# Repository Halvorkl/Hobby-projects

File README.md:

# Hobby-projects

This repository contains smaller hobby projects I've worked on, mainly within electronics and hardware design.

I mostly focus on:

- PCB design
- IC design
- General system design (electronics and embedded-related)

The projects here are experiments, prototypes, and explorations of different ideas and design techniques.

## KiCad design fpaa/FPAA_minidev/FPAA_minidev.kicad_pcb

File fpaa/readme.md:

## FPAA dev board

In this project, I have designed a compact development board for the AN231.

The AN231 is a Field Programmable Analog Array (FPAA) based on a switched-capacitor architecture. It enables a programmable analog front-end in your design, allowing the same hardware to be repurposed for different analog signal processing tasks.

This project provides a simple, compact PCB that can be easily integrated into other designs. The board has a form factor of ~47x21.2mm, and the I/O connections are kept as straightforward as possible to simplify prototyping and implementation.

<p float="left">
  
  &nbsp;&nbsp;
  
</p>

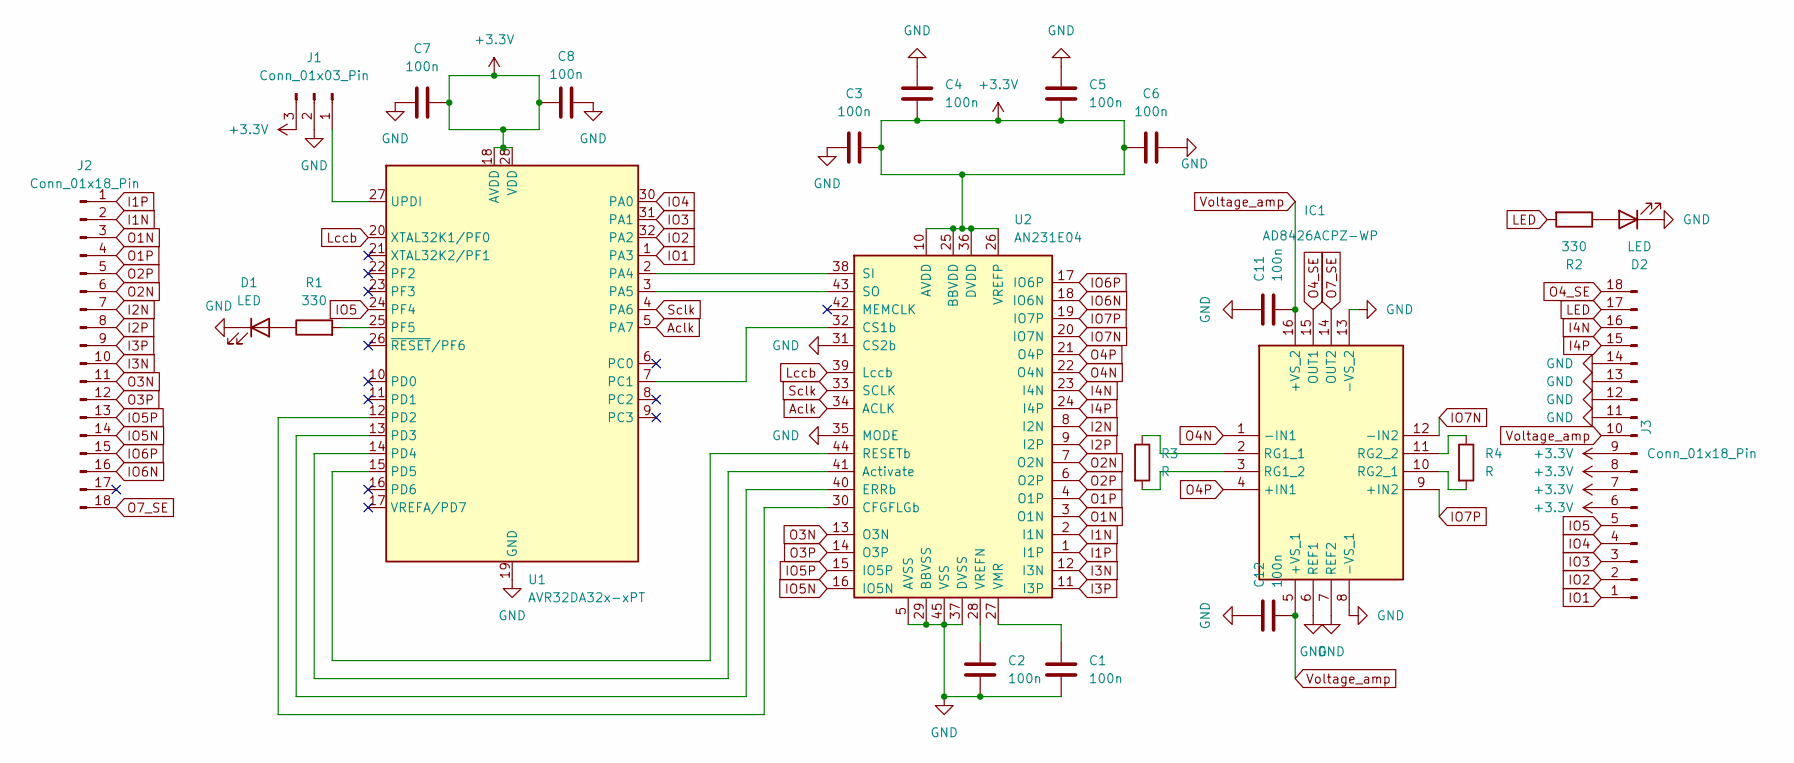
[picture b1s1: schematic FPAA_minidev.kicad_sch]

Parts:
C1, C2, C3, C4, C5, C6, C7, C8, C11, C12: 100n; C_0603_1608Metric
D1, D2: LED; LED_0603_1608Metric
IC1: AD8426ACPZ-WP; QFN65P400X400X100-16N-D; Mouser Part Number 584-AD8426ACPZ-WP
J1: Conn_01x03_Pin; PinHeader_1x03_P2.54mm_Vertical
J2, J3: Conn_01x18_Pin; PinHeader_1x18_P2.54mm_Vertical
R1, R2: 330; C_0603_1608Metric
R3, R4: R; C_0603_1608Metric
U1: AVR32DA32x-xPT; TQFP-32_7x7mm_P0.8mm
U2: AN231E04; QFN-44-1EP_9x9mm_P0.65mm_EP7.5x7.5mm

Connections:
+3.3V: C3.1, C4.2, C5.2, C6.1, C7.2, C8.1, J1.3, J3.6, J3.7, J3.8, J3.9, U1.18 (AVDD), U1.28 (VDD), U2.10 (AVDD), U2.25 (BBVDD), U2.26 (VREFP), U2.36 (DVDD)
Aclk: U1.5 (PA7), U2.34 (ACLK)
GND: C1.2, C2.2, C3.2, C4.1, C5.1, C6.2, C7.1, C8.2, C11.1, C12.1, D1.1 (K), D2.1 (K), IC1.6 (REF1), IC1.7 (REF2), IC1.8 (-VS_1), IC1.13 (-VS_2), J1.2, J3.11, J3.12, J3.13, J3.14, U1.19 (GND), U1.29 (GND), U2.5 (AVSS), U2.29 (BBVSS), U2.31 (CS2b), U2.35 (MODE), U2.37 (DVSS), U2.45 (VSS)
I1N: J2.2, U2.2 (I1N)
I1P: J2.1, U2.1 (I1P)
I2N: J2.7, U2.8 (I2N)
I2P: J2.8, U2.9 (I2P)
I3N: J2.10, U2.12 (I3N)
I3P: J2.9, U2.11 (I3P)
I4N: J3.16, U2.23 (I4N)
I4P: J3.15, U2.24 (I4P)
IO1: J3.1, U1.1 (PA3)
IO2: J3.2, U1.32 (PA2)
IO3: J3.3, U1.31 (PA1)
IO4: J3.4, U1.30 (PA0)
IO5: J3.5, U1.24 (PF4)
IO5N: J2.14, U2.16 (IO5N)
IO5P: J2.13, U2.15 (IO5P)
IO6N: J2.16, U2.18 (IO6N)
IO6P: J2.15, U2.17 (IO6P)
IO7N: IC1.12 (-IN2), U2.20 (IO7N)
IO7P: IC1.9 (+IN2), U2.19 (IO7P)
LED: J3.17, R2.2
Lccb: U1.20 (XTAL32K1/PF0), U2.39 (Lccb)
unnamed: D1.2 (A), R1.1
unnamed: D2.2 (A), R2.1
unnamed: IC1.2 (RG1_1), R3.1
unnamed: IC1.3 (RG1_2), R3.2
unnamed: IC1.10 (RG2_1), R4.2
unnamed: IC1.11 (RG2_2), R4.1
unnamed: J1.1, U1.27 (UPDI)
unnamed: U1.2 (PA4), U2.38 (SI)
unnamed: U1.3 (PA5), U2.43 (SO)
unnamed: U1.7 (PC1), U2.32 (CS1b)
unnamed: U1.12 (PD2), U2.30 (CFGFLGb)
unnamed: U1.13 (PD3), U2.40 (ERRb)
unnamed: U1.14 (PD4), U2.41 (Activate)
unnamed: U1.15 (PD5), U2.44 (RESETb)
unnamed: R1.2, U1.25 (PF5)
unnamed: C1.1, U2.27 (VMR)
unnamed: C2.1, U2.28 (VREFN)
O1N: J2.3, U2.3 (O1N)
O1P: J2.4, U2.4 (O1P)
O2N: J2.6, U2.7 (O2N)
O2P: J2.5, U2.6 (O2P)
O3N: J2.11, U2.13 (O3N)
O3P: J2.12, U2.14 (O3P)
O4N: IC1.1 (-IN1), U2.22 (O4N)
O4P: IC1.4 (+IN1), U2.21 (O4P)
O4_SE: IC1.15 (OUT1), J3.18
O7_SE: IC1.14 (OUT2), J2.18
Sclk: U1.4 (PA6), U2.33 (SCLK)
Voltage_amp: C11.2, C12.2, IC1.5 (+VS_1), IC1.16 (+VS_2), J3.10

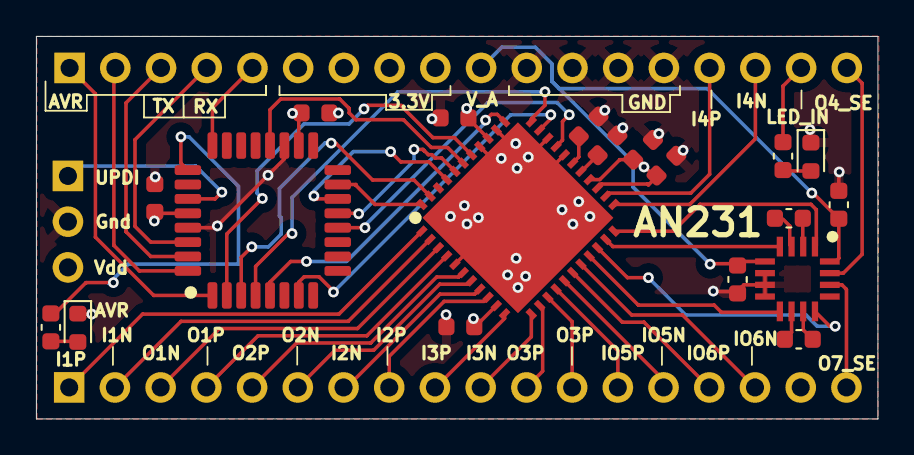
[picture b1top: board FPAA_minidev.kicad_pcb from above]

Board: 4 copper layers, 46.8 x 21.2 mm, 22 parts (0 on the bottom side), 53 nets.

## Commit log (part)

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2026-06-21 Enhance README with project descriptions and focus areas
    Expanded the README to provide more details about the projects.
2026-06-21 Add initial README for Radar project
2026-06-21 Add description to radar project README
2026-06-21 Update readme for clarity and formatting
2026-06-21 Add readme for 5 GHz CW radar project
    This document outlines the objectives and focus areas of the 5 GHz CW radar project, emphasizing the analog front-end design.
2026-06-21 Create README for Wi-Fi radar project
    Added project overview and goals for Wi-Fi radar.
2026-06-21 Update readme to clarify signal source description
2026-06-21 Create README for FPAA development board
    Added a README file for the FPAA development board, detailing its design and functionality.
2026-06-21 Add readme for Lyra – GHOST mission communications system
    Added project overview and details about the CubeSat communications system.
2026-06-21 Added pcb and belonging files
2026-06-21 zipped pcb files
2026-06-21 Include front view image in readme
    Add image reference for PCB front view in readme.
2026-06-21 Fix image filename case in readme.md
2026-06-21 Improve layout of PCB images in readme
    Added margin to the front PCB image for better layout.
2026-06-21 Adjust image margin in readme
    Updated the margin of the front PCB image for better layout.
2026-06-21 Adjust PCB image layout in readme
    Removed excessive margin from front PCB image.
2026-06-21 Enhance readme with image descriptions
    Added descriptions for front and back images of PCB.
2026-06-21 Update readme.md to improve PCB image display
    Replaced old image formatting with a table layout for better presentation.
2026-06-21 Fix image source case in readme.md
2026-06-21 Revise PCB images in readme for better layout
    Updated the readme to change the image format and layout.
2026-06-21 small changes
